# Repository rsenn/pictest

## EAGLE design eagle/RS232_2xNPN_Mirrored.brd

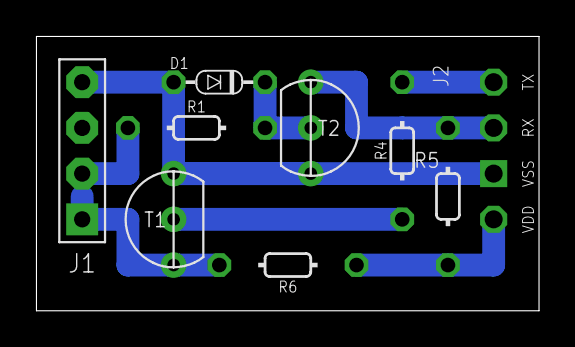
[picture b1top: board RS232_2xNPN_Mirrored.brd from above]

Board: 2 copper layers, 27.9 x 15.2 mm, 9 parts (0 on the bottom side), 8 nets.

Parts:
D1: 1N4148; DO34-5
J1: COMPORT-4PIN-NEW; RS232-4PIN-NEW
J2: PIC-UART-X
R1: 4.7kΩ; 0202/7
R4: 10kΩ; 0202/7
R5: 1kΩ; 0202/7-V
R6: 1kΩ; 0202/7
T1, T2: BC547; TO92-CBE

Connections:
+5V: J2.20, R5.2, R6.2
GND: D1.A, J1.4, J2.19, T1.E, T2.E
unnamed: J2.18, R5.1, T2.C
unnamed: D1.C, R1.1, T2.B
unnamed: J1.2, R1.2
unnamed: J2.17, R4.1
unnamed: R4.2, T1.B
unnamed: J1.1, R6.1, T1.C

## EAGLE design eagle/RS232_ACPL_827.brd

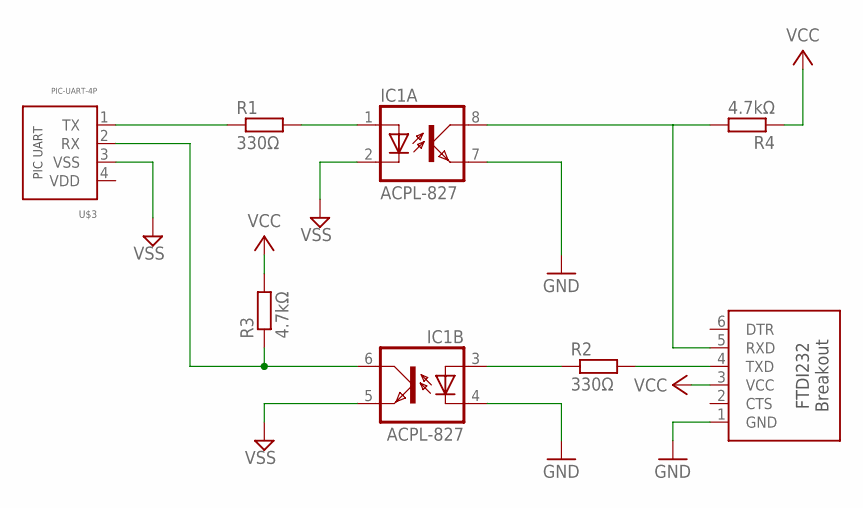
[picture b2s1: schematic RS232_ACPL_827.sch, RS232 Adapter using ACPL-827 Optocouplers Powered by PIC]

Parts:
IC1: ACPL-827; DIL08
R1: 330Ω; 0207/10
R2: 330Ω; 0204/7
R3, R4: 4.7kΩ; 0204/7
U$2: FTDI232-BO-6P; CONN-6P
U$3: PIC-UART-4P; CONN-4P

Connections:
GND: IC1.4 (C), IC1.7 (EMIT), U$2.1 (GND)
unnamed: IC1.1 (A), R1.2
unnamed: R1.1, U$3.1 (TX)
unnamed: IC1.3 (A), R2.1
unnamed: R2.2, U$2.4 (TXD)
unnamed: IC1.6 (COL), R3.1, U$3.2 (RX)
unnamed: IC1.8 (COL), R4.2, U$2.5 (RXD)
VCC: R3.2, R4.1, U$2.3 (VCC)
VSS: IC1.2 (C), IC1.5 (EMIT), U$3.3 (VSS)

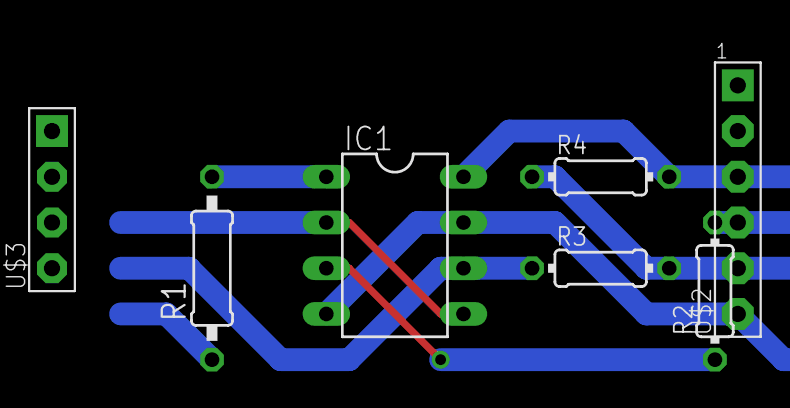
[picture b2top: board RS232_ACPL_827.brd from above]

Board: 2 copper layers, 7 parts (0 on the bottom side), 9 nets.

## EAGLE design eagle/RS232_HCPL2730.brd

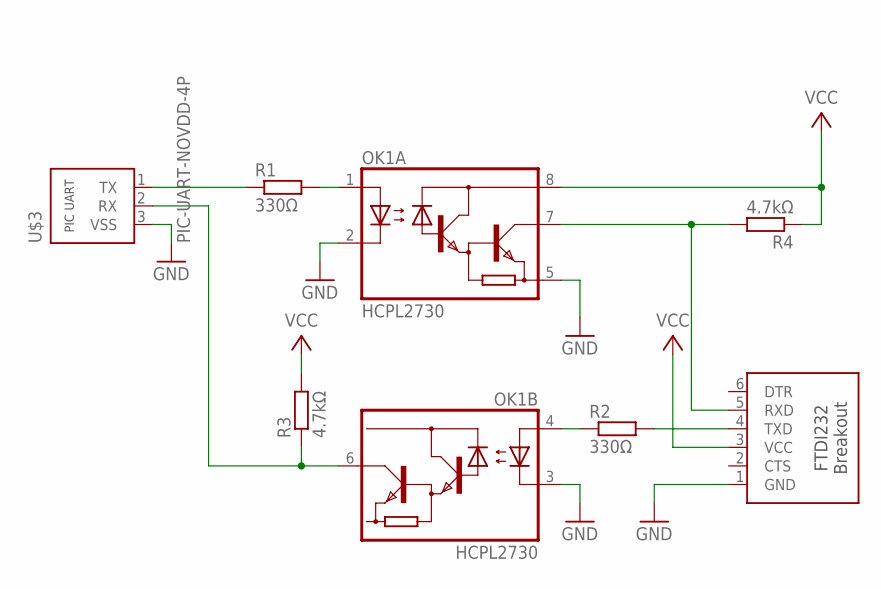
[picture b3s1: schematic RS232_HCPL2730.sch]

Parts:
OK1: HCPL2730; DIL08
R1: 330Ω; 0207/10
R2: 330Ω; 0204/7
R3, R4: 4.7kΩ; 0204/7
U$2: FTDI232-BO-6P; CONN-6P
U$3: PIC-UART-NOVDD-4P; CONN-4P

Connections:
GND: OK1.2 (C1), OK1.3 (C2), OK1.5 (GND), U$2.1 (GND), U$3.3 (VSS)
unnamed: OK1.1 (A1), R1.2
unnamed: R1.1, U$3.1 (TX)
unnamed: OK1.4 (A2), R2.1
unnamed: R2.2, U$2.4 (TXD)
unnamed: OK1.6 (VO2), R3.1, U$3.2 (RX)
unnamed: OK1.7 (VO1), R4.2, U$2.5 (RXD)
VCC: OK1.8 (VCC), R3.2, R4.1, U$2.3 (VCC)

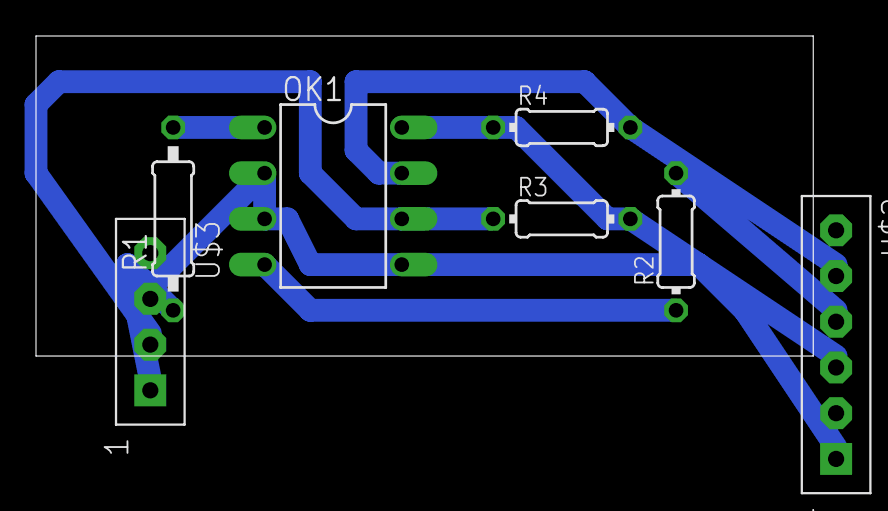
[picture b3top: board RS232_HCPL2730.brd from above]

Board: 2 copper layers, 43.2 x 17.8 mm, 7 parts (0 on the bottom side), 8 nets.

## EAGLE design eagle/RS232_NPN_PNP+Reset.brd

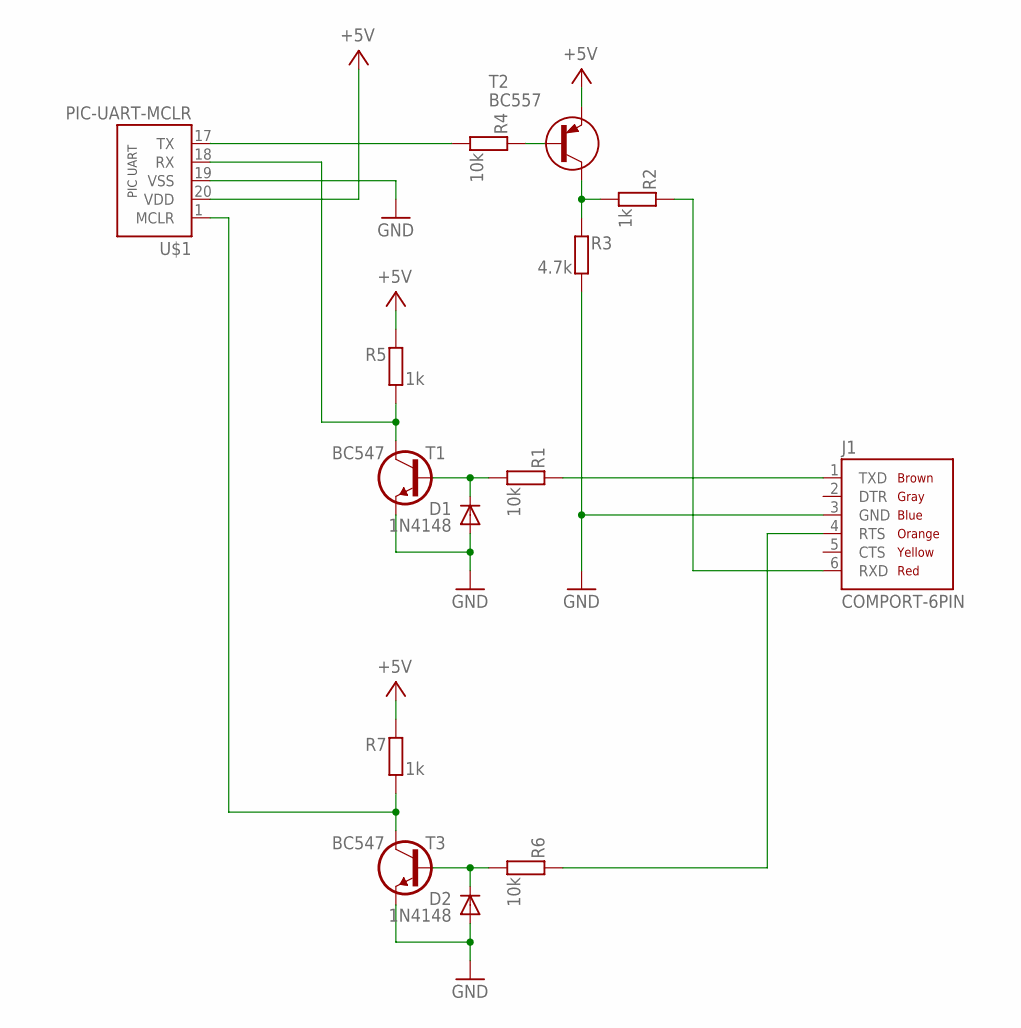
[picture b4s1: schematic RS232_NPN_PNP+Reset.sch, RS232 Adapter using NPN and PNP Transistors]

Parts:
D1, D2: 1N4148; DO34-5
J1: COMPORT-6PIN; RS232-6PIN
R1, R4, R6: 10k; 0202/5
R2, R5: 1k; 0202/5
R3: 4.7k; 0202/5
R7: 1k; 0202/2V
T1, T3: BC547; TO92-CBE
T2: BC557; TO92-CBE
U$1: PIC-UART-MCLR

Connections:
+5V: R5.2, R7.2, T2.E, U$1.20 (VDD)
GND: D1.A, D2.A, J1.3 (GND), R3.1, T1.E, T3.E, U$1.19 (VSS)
unnamed: R5.1, T1.C, U$1.18 (RX)
unnamed: D1.C, R1.1, T1.B
unnamed: J1.1 (TXD), R1.2
unnamed: R4.1, U$1.17 (TX)
unnamed: R4.2, T2.B
unnamed: R2.1, R3.2, T2.C
unnamed: J1.6 (RXD), R2.2
unnamed: R7.1, T3.C, U$1.1 (MCLR)
unnamed: D2.C, R6.1, T3.B
unnamed: J1.4 (RTS), R6.2

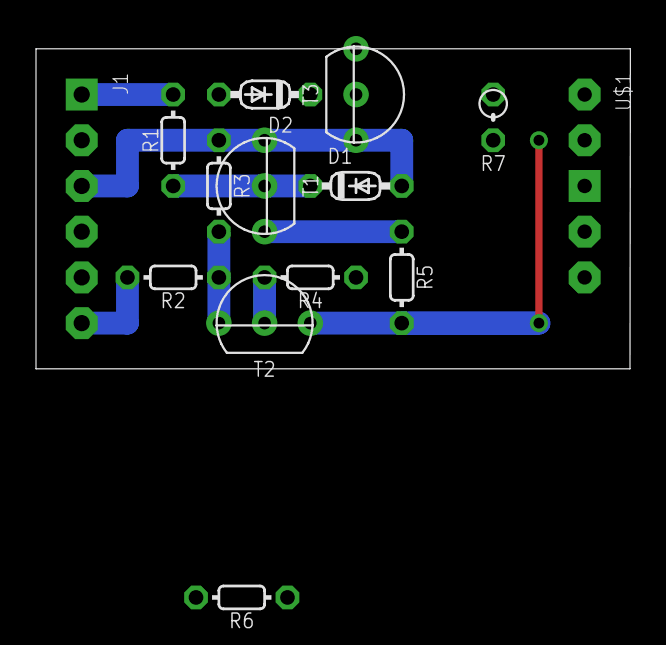
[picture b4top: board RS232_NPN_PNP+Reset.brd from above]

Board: 2 copper layers, 33.0 x 17.8 mm, 14 parts (0 on the bottom side), 12 nets.

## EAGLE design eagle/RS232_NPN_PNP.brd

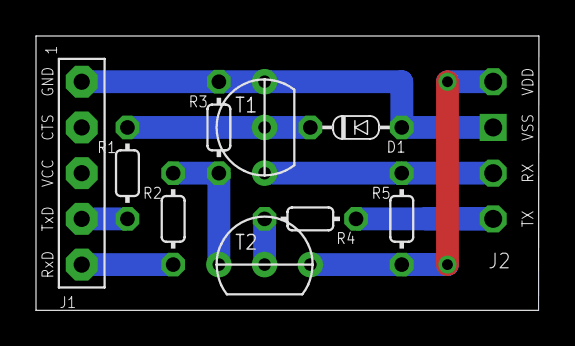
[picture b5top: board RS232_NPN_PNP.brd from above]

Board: 2 copper layers, 27.9 x 15.2 mm, 10 parts (0 on the bottom side), 9 nets.

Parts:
D1: 1N4148; DO34-5
J1: FTDI232; FTDI232-BO-5-L
J2: PIC-UART
R1: 10kΩ; 0202/5-V
R2, R5: 1kΩ; 0202/5-V
R3: 4.7kΩ; 0202/5-V
R4: 10kΩ; 0202/5
T1: BC547; TO92-CBE
T2: BC557; TO92-CBE

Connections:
+5V: J2.20, R5.2, T2.E
GND: D1.A, J1.GND, J2.19, R3.1, T1.E
unnamed: J2.18, R5.1, T1.C
unnamed: D1.C, R1.1, T1.B
unnamed: J1.TXD, R1.2
unnamed: J2.17, R4.1
unnamed: R4.2, T2.B
unnamed: R2.1, R3.2, T2.C
unnamed: J1.RXD, R2.2

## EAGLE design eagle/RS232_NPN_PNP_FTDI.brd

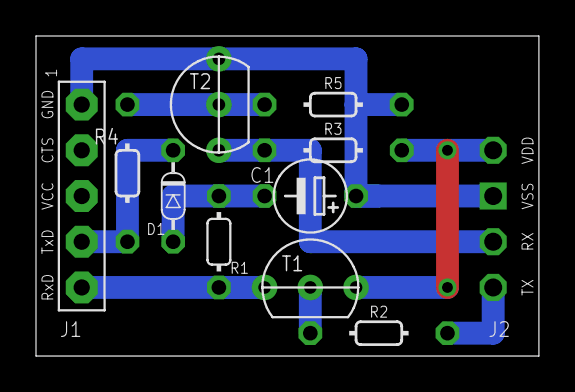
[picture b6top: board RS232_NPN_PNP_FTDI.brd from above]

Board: 2 copper layers, 27.9 x 17.8 mm, 11 parts (0 on the bottom side), 9 nets.

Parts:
C1: 10μF; E5-4
D1: 1N4148; DO34-5V
J1: FTDI232-BO-5P-L; FTDI232-BO-5-L
J2: PIC-UART
R1: 10kΩ; 0202/5-V
R2, R3, R5: 10kΩ; 0202/7
R4: 10kΩ; 0202/7-V
T1: BC557; TO92-CBE
T2: BC547; TO92-CBE

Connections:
-12V: C1.-, D1.A, R1.2
GND: C1.+, J1.GND, J2.19, R5.1, T2.E
unnamed: R2.2, T1.B
unnamed: R4.1, R5.2, T2.B
RX: J2.18, R3.2, T2.C
RXD: J1.RXD, R1.1, T1.C
TX: J2.17, R2.1
TXD: D1.C, J1.TXD, R4.2
VCC: J2.20, R3.1, T1.E
